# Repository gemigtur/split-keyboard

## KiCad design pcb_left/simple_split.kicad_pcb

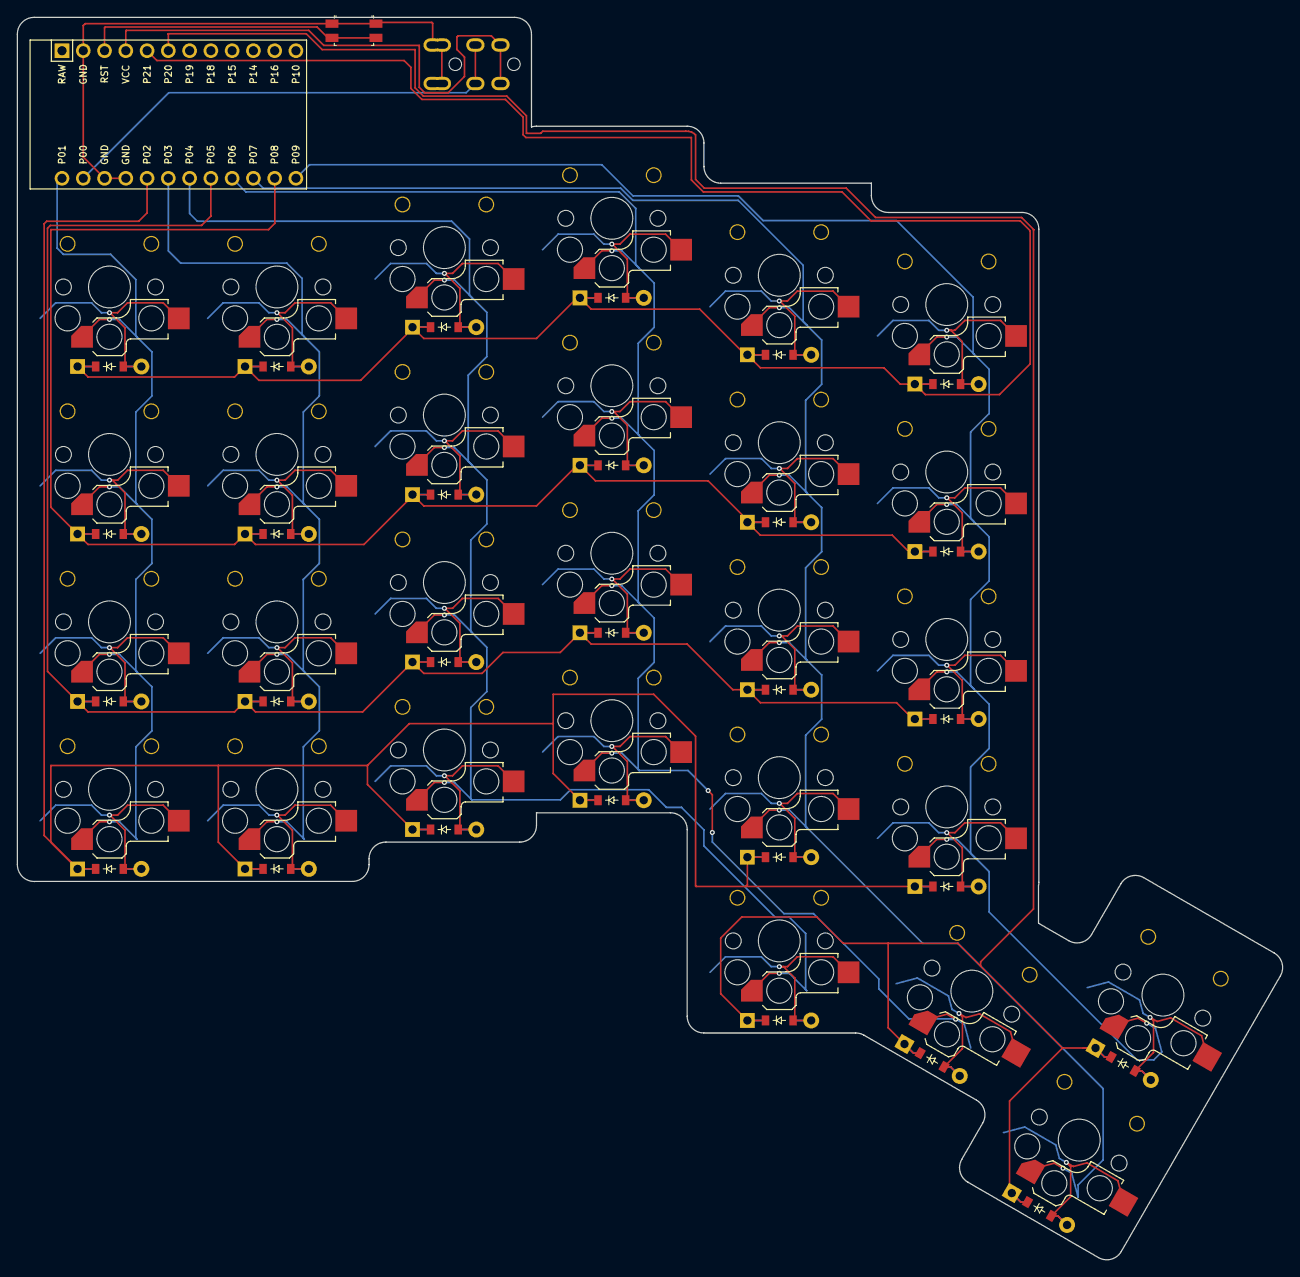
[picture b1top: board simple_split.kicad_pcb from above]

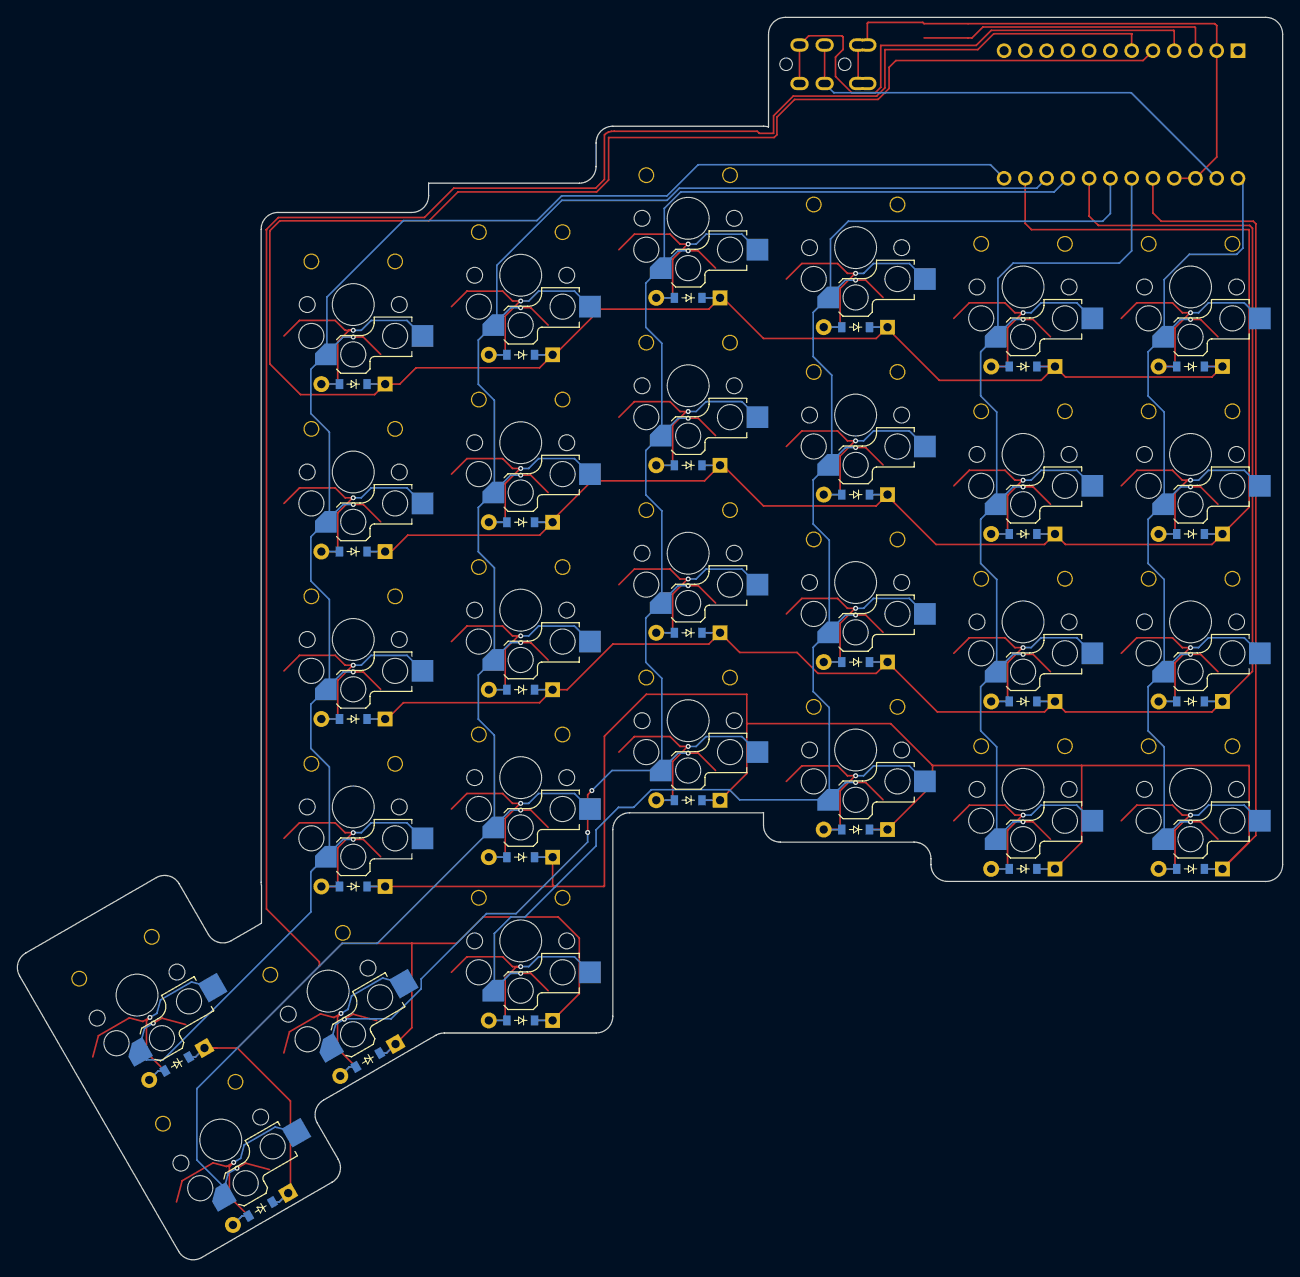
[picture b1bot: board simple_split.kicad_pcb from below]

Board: 2 copper layers, 151.1 x 148.4 mm, 59 parts (28 on the bottom side), 43 nets.

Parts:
D1, D2, D3, D4, D5, D6, D7, D8, D9, D10, D11, D12, D13, D14, D15, D16, D17, D18, D19, D20, D21, D22, D23, D24, D25, D26, D27, D28: ComboDiode
MCU1: ProMicro
RST1: reset_switch_smd_side
S1, S2, S3, S4, S5, S6, S7, S8, S9, S10, S11, S12, S13, S14, S15, S16, S17, S18, S19, S20, S21, S22, S23, S24, S25, S26, S27, S28: switch_choc_v1_v2
TRRS1: TRRS-PJ-320A-dual

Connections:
GND: MCU1.2, MCU1.15, MCU1.16, RST1.1, RST1.3, TRRS1.1, TRRS1.2
P0: MCU1.14, TRRS1.3
P1: MCU1.13, S1.1, S2.1, S3.1, S4.1
P2: D1.1, D5.1, D9.1, D13.1, D17.1, D21.1, MCU1.17
P3: MCU1.18, S5.1, S6.1, S7.1, S8.1
P4: MCU1.19, S9.1, S10.1, S11.1, S12.1, S25.1
P5: D2.1, D6.1, D10.1, D14.1, D18.1, D22.1, MCU1.20
P6: MCU1.21, S13.1, S14.1, S15.1, S16.1, S26.1
P7: MCU1.22, S17.1, S18.1, S19.1, S20.1, S27.1
P8: D3.1, D7.1, D11.1, D15.1, D19.1, D23.1, MCU1.23
P9: MCU1.24, S21.1, S22.1, S23.1, S24.1, S28.1
P20: D25.1, D26.1, D27.1, D28.1, MCU1.6
P21: D4.1, D8.1, D12.1, D16.1, D20.1, D24.1, MCU1.5
RST: MCU1.3, RST1.2, RST1.4
VCC: MCU1.4, TRRS1.4
index_bottom: D17.2, S17.2
index_home: D18.2, S18.2
index_num: D20.2, S20.2
index_top: D19.2, S19.2
inner_bottom: D21.2, S21.2
inner_home: D22.2, S22.2
inner_num: D24.2, S24.2
inner_top: D23.2, S23.2
middle_bottom: D13.2, S13.2
middle_home: D14.2, S14.2
middle_num: D16.2, S16.2
middle_top: D15.2, S15.2
outer_bottom: D1.2, S1.2
outer_home: D2.2, S2.2
outer_num: D4.2, S4.2
outer_top: D3.2, S3.2
pinkey_bottom: D5.2, S5.2
pinkey_home: D6.2, S6.2
pinkey_num: D8.2, S8.2
pinkey_top: D7.2, S7.2
ring_bottom: D9.2, S9.2
ring_home: D10.2, S10.2
ring_num: D12.2, S12.2
ring_top: D11.2, S11.2
thumb_left_key: D25.2, S25.2
thumb_middle_key: D26.2, S26.2
thumb_right_key: D27.2, S27.2
thumb_top_key: D28.2, S28.2

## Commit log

2026-03-03 Update: pcbs routed
2026-03-12 Update: pcb wired
2026-03-12 Update: gerber for left pcb
2026-04-11 Chore: clean up
